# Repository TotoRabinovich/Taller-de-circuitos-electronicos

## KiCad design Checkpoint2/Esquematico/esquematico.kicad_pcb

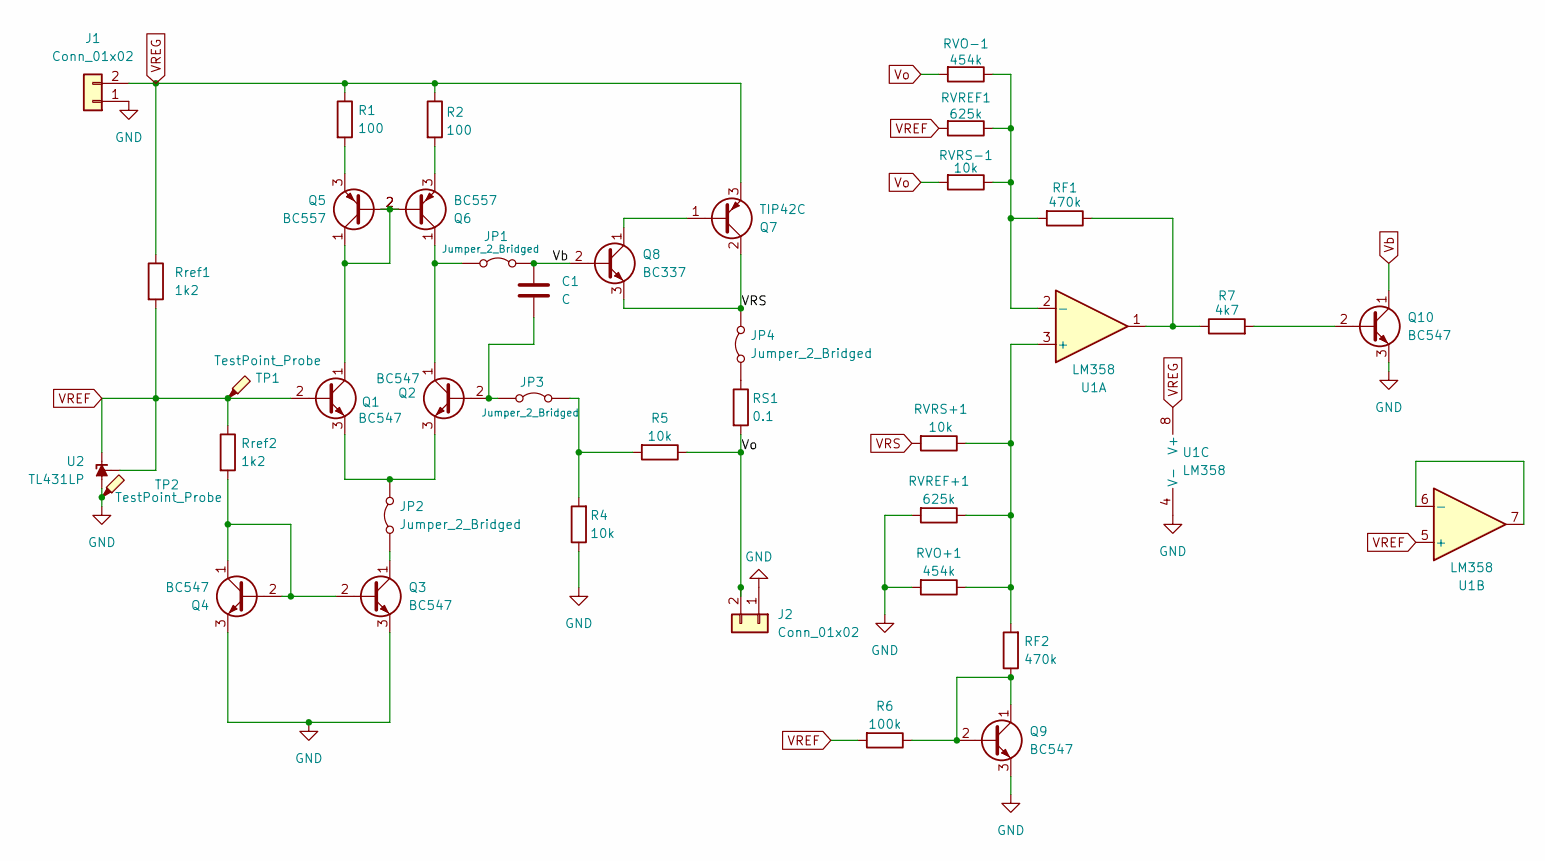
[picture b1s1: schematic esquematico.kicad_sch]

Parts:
C1: C; C_Disc_D4.3mm_W1.9mm_P5.00mm
J1, J2: Conn_01x02; Samtec_HPM-02-01-x-S_Straight_1x02_Pitch5.08mm
JP1, JP2, JP3, JP4: Jumper_2_Bridged; TestPoint_2Pads_Pitch2.54mm_Drill0.8mm
Q1, Q2, Q3, Q4, Q9, Q10: BC547; TO-92_Wide
Q5, Q6: BC557; TO-92_Wide
Q7: TIP42C; TO-220-3_Vertical
Q8: BC337; TO-92_Wide
R1, R2: 100; R_Axial_DIN0309_L9.0mm_D3.2mm_P12.70mm_Horizontal
R4, R5: 10k; R_Axial_DIN0309_L9.0mm_D3.2mm_P12.70mm_Horizontal
R6: 100k; R_Axial_DIN0309_L9.0mm_D3.2mm_P12.70mm_Horizontal
R7: 4k7; R_Axial_DIN0309_L9.0mm_D3.2mm_P12.70mm_Horizontal
RF1, RF2: 470k; R_Axial_DIN0309_L9.0mm_D3.2mm_P12.70mm_Horizontal
RS1: 0.1; R_Axial_Power_L25.0mm_W6.4mm_P27.94mm
RVO+1: 454k; R_Axial_DIN0309_L9.0mm_D3.2mm_P12.70mm_Horizontal
RVO-1: 454k; R_Axial_DIN0309_L9.0mm_D3.2mm_P12.70mm_Horizontal
RVREF1: 625k; R_Axial_DIN0309_L9.0mm_D3.2mm_P12.70mm_Horizontal
RVREF+1: 625k; R_Axial_DIN0309_L9.0mm_D3.2mm_P12.70mm_Horizontal
RVRS+1: 10k; R_Axial_DIN0309_L9.0mm_D3.2mm_P12.70mm_Horizontal
RVRS-1: 10k; R_Axial_DIN0309_L9.0mm_D3.2mm_P12.70mm_Horizontal
Rref1, Rref2: 1k2; R_Axial_DIN0309_L9.0mm_D3.2mm_P12.70mm_Horizontal
TP1, TP2: TestPoint_Probe; TestPoint_Keystone_5000-5004_Miniature
U1: LM358; DIP-8_W7.62mm_LongPads
U2: TL431LP; TO-92_Wide

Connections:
GND: J1.1, J2.1, Q3.3 (E), Q4.3 (E), Q9.3 (E), Q10.3 (E), R4.1, RVO+1.2, RVREF+1.2, TP2.1 (1_1), U1.4 (V-), U2.2 (A)
unnamed: JP1.1 (A), Q2.1 (C), Q6.1 (C)
unnamed: JP2.1 (A), Q3.1 (C)
unnamed: JP2.2 (B), Q1.3 (E), Q2.3 (E)
unnamed: C1.2, JP3.1 (A), Q2.2 (B)
unnamed: JP3.2 (B), R4.2, R5.2
unnamed: JP4.1 (A), RS1.1
unnamed: Q1.1 (C), Q5.1 (C), Q5.2 (B), Q6.2 (B)
unnamed: Q3.2 (B), Q4.1 (C), Q4.2 (B), Rref2.2
unnamed: Q5.3 (E), R1.2
unnamed: Q6.3 (E), R2.2
unnamed: Q7.1 (B), Q8.1 (C)
unnamed: Q9.1 (C), Q9.2 (B), R6.1, RF2.1
unnamed: Q10.2 (B), R7.2
unnamed: R7.1, RF1.1, U1.1
unnamed: RF2.2, RVO+1.1, RVREF+1.1, RVRS+1.1, U1.3 (+)
unnamed: RF1.2, RVO-1.1, RVREF1.1, RVRS-1.1, U1.2 (-)
unnamed: U1.6 (-), U1.7
VREF: Q1.2 (B), R6.2, RVREF1.2, Rref1.2, Rref2.1, TP1.1 (1_1), U1.5 (+), U2.1 (REF), U2.3 (K)
VREG: J1.2, Q7.3 (E), R1.1, R2.1, Rref1.1, U1.8 (V+)
VRS: JP4.2 (B), Q7.2 (C), Q8.3 (E), RVRS+1.2
Vb: C1.1, JP1.2 (B), Q8.2 (B), Q10.1 (C)
Vo: J2.2, R5.1, RS1.2, RVO-1.2, RVRS-1.2

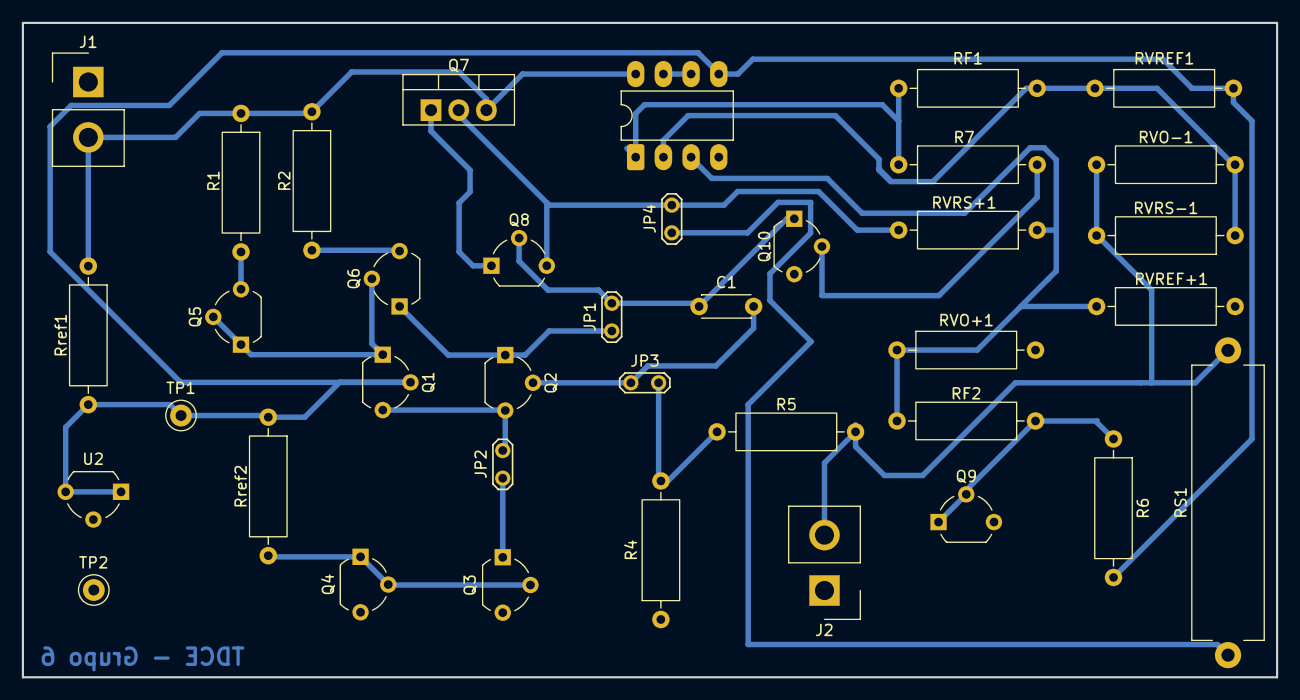
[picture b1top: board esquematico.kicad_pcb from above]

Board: 2 copper layers, 115.0 x 60.0 mm, 38 parts (0 on the bottom side), 23 nets.
